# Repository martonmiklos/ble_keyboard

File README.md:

View this project on [CADLAB.io](https://cadlab.io/project/2062). 

# ble_keyboard

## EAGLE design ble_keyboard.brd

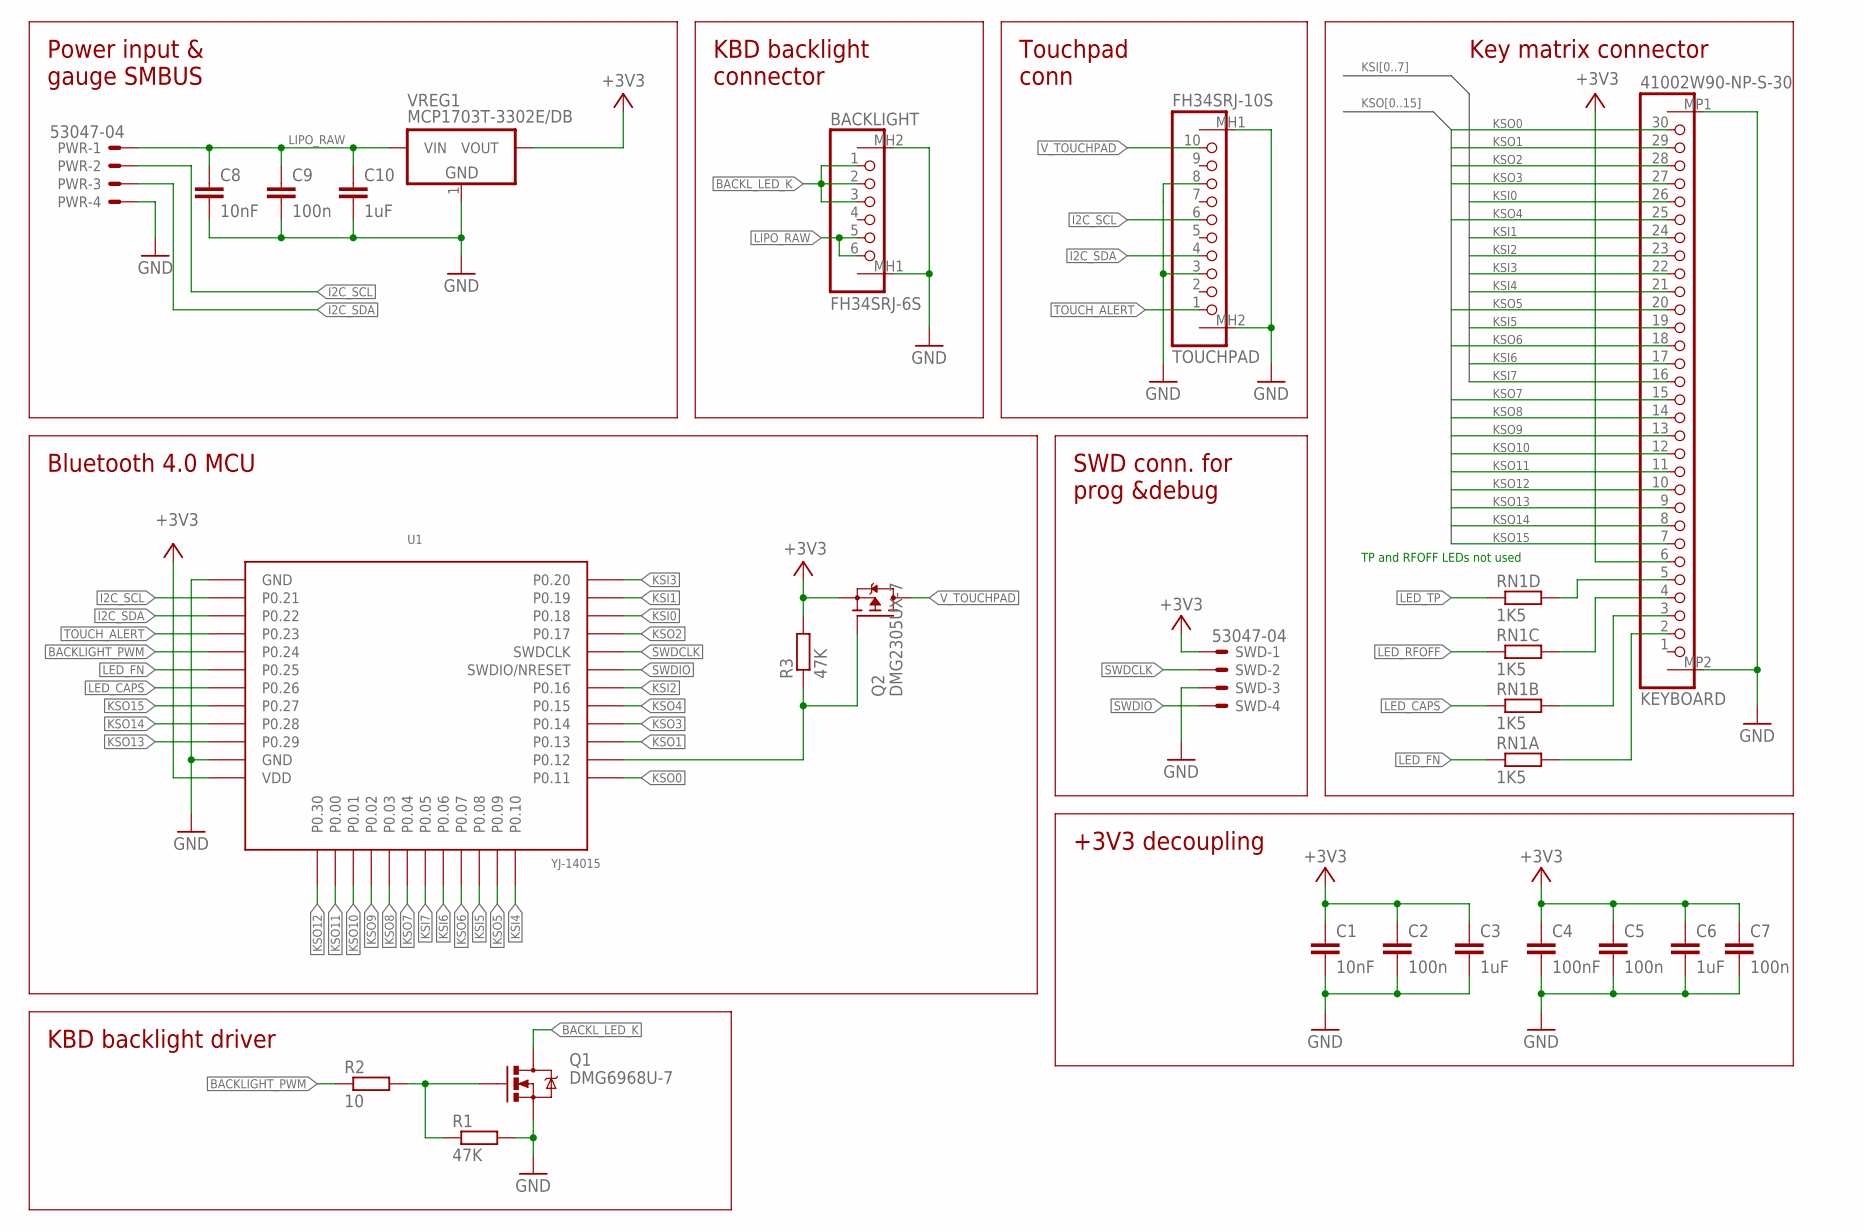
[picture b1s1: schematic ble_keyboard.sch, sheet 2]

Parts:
BACKLIGHT: FH34SRJ-6S
C1, C8: 10nF; C0603
C2, C5, C7, C9: 100n; C0603
C3, C6, C10: 1uF; C0603
C4: 100nF; C0603
KEYBOARD: 41002W90-NP-S-30; 41200W90-NP-S
PWR: 53047-04
Q1: DMG6968U-7; SOT23-3
Q2: DMG2305UX-7; SOT23
R1, R3: 47K; R0603
R2: 10; R0603
RN1: 1K5; RN8P-4R-CRA06S
SWD: 53047-04
TOUCHPAD: FH34SRJ-10S
U1: YJ-14015
VREG1: MCP1703T-3302E/DB; SOT-223

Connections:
+3V3: C1.1, C2.1, C3.1, C4.1, C5.1, C6.1, C7.1, KEYBOARD.6, Q2.3 (S), R3.2, SWD.1, U1.VDD, VREG1.2 (VOUT)
BACKLIGHT_PWM: R2.1, U1.P.24 (P0.24)
BACKL_LED_K: BACKLIGHT.1, BACKLIGHT.2, BACKLIGHT.3, Q1.3 (D)
GND: BACKLIGHT.MH1, BACKLIGHT.MH2, C1.2, C2.2, C3.2, C4.2, C5.2, C6.2, C7.2, C8.2, C9.2, C10.2, KEYBOARD.MP1, KEYBOARD.MP2, PWR.4, Q1.2 (S), R1.2, SWD.3, TOUCHPAD.3, TOUCHPAD.8, TOUCHPAD.MH1, TOUCHPAD.MH2, U1.GND, U1.GND@2 (GND), VREG1.1 (GND)
I2C_SCL: PWR.2, TOUCHPAD.6, U1.P.21 (P0.21)
I2C_SDA: PWR.3, TOUCHPAD.4, U1.P.22 (P0.22)
KSI0: KEYBOARD.26, U1.P.18 (P0.18)
KSI1: KEYBOARD.24, U1.P.19 (P0.19)
KSI2: KEYBOARD.23, U1.P.16 (P0.16)
KSI3: KEYBOARD.22, U1.P.20 (P0.20)
KSI4: KEYBOARD.21, U1.P.10 (P0.10)
KSI5: KEYBOARD.19, U1.P.08 (P0.08)
KSI6: KEYBOARD.17, U1.P.06 (P0.06)
KSI7: KEYBOARD.16, U1.P.05 (P0.05)
KSO0: KEYBOARD.30, U1.P.11 (P0.11)
KSO1: KEYBOARD.29, U1.P.13 (P0.13)
KSO2: KEYBOARD.28, U1.P.17 (P0.17)
KSO3: KEYBOARD.27, U1.P.14 (P0.14)
KSO4: KEYBOARD.25, U1.P.15 (P0.15)
KSO5: KEYBOARD.20, U1.P.09 (P0.09)
KSO6: KEYBOARD.18, U1.P.07 (P0.07)
KSO7: KEYBOARD.15, U1.P.04 (P0.04)
KSO8: KEYBOARD.14, U1.P.03 (P0.03)
KSO9: KEYBOARD.13, U1.P.02 (P0.02)
KSO10: KEYBOARD.12, U1.P.01 (P0.01)
KSO11: KEYBOARD.11, U1.P.00 (P0.00)
KSO12: KEYBOARD.10, U1.P.30 (P0.30)
KSO13: KEYBOARD.9, U1.P.29 (P0.29)
KSO14: KEYBOARD.8, U1.P.28 (P0.28)
KSO15: KEYBOARD.7, U1.P.27 (P0.27)
LED_CAPS: RN1.2 (1), U1.P.26 (P0.26)
LED_CAPS_R: KEYBOARD.3, RN1.7 (2)
LED_FN: RN1.1, U1.P.25 (P0.25)
LED_FN_R: KEYBOARD.2, RN1.8 (2)
LED_RFOFF: RN1.3 (1)
LED_RFOFF_R: KEYBOARD.4, RN1.6 (2)
LED_TP: RN1.4 (1)
LED_TP_R: KEYBOARD.5, RN1.5 (2)
LIPO_RAW: BACKLIGHT.5, BACKLIGHT.6, C8.1, C9.1, C10.1, PWR.1, VREG1.3 (VIN)
MOTOR_A_GATE_R: Q1.1 (G), R1.1, R2.2
NENABLE_TOUCHPAD: Q2.1 (G), R3.1, U1.P.12 (P0.12)
SWDCLK: SWD.2, U1.SWDCLK
SWDIO: SWD.4, U1.SWDIO (SWDIO/NRESET)
TOUCH_ALERT: TOUCHPAD.1, U1.P.23 (P0.23)
V_TOUCHPAD: Q2.2 (D), TOUCHPAD.10

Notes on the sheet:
SWD conn. for prog &debug
KBD backlight connector
Touchpad conn
Key matrix connector
Bluetooth 4.0 MCU
Power input & gauge SMBUS
+3V3 decoupling
KBD backlight driver
TP and RFOFF LEDs not used

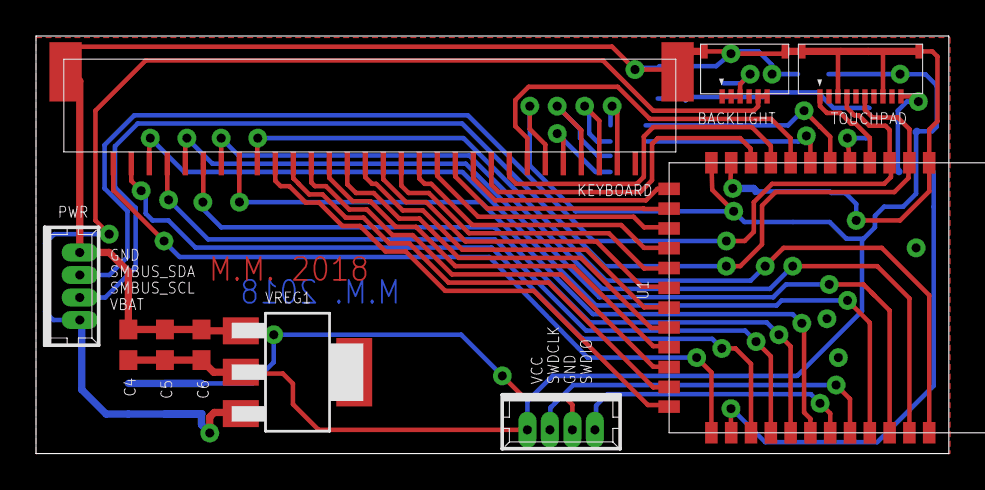
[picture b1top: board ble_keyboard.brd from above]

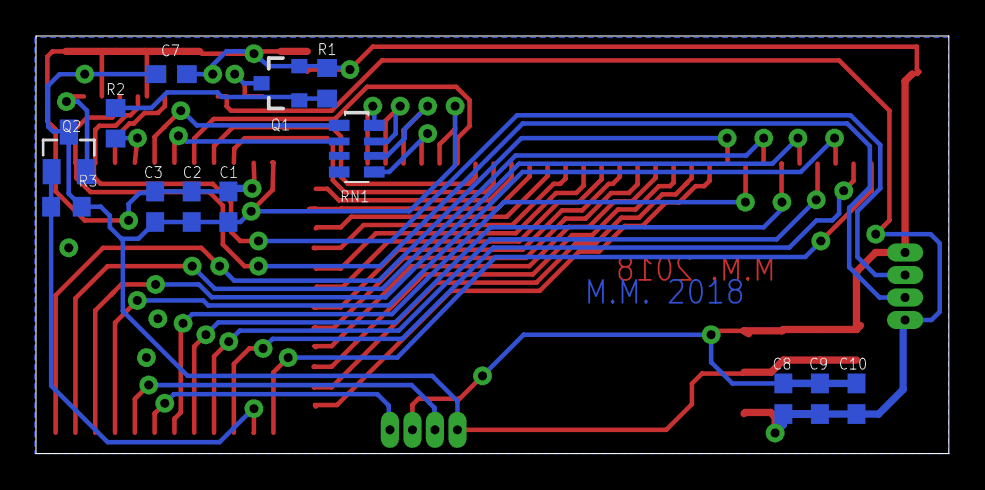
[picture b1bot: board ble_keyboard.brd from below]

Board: 2 copper layers, 50.7 x 23.2 mm, 23 parts (13 on the bottom side), 43 nets.

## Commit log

2017-09-05 Added cad files
2017-09-13 BRD routed
2017-09-16 - Save before BLE module rotation. - Added note abotu the best antenna gain.
2017-09-17 Brd routed with 90 degree rotated BLE module, fixed touchpad and Keyboard pinout
2017-09-17 Cleaned up schematic mess, fixed keyboard BL pinout mirroring.
2017-10-12 Sikscreen cleanup before Gerberization
2018-02-06 Updated BT module footprint
2018-08-08 Schematic cleanup
2018-08-08 - Fix P ch FET footprint - Add a note about unconnected LEDs
2019-08-22 Backlink to CADLAB.io has been added.

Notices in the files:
parts and their libraries:
SparkFun: Licensing: CC v3.0 Share-Alike You are welcome to use this library for commercial purposes.
